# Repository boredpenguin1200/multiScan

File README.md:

# multiScan
Multispectral scanning using a 3d printer

This project is under heavy development, all hardware/software is experimental

software requires openCV with python bindings, tested/developed on linux but should be windows compatible

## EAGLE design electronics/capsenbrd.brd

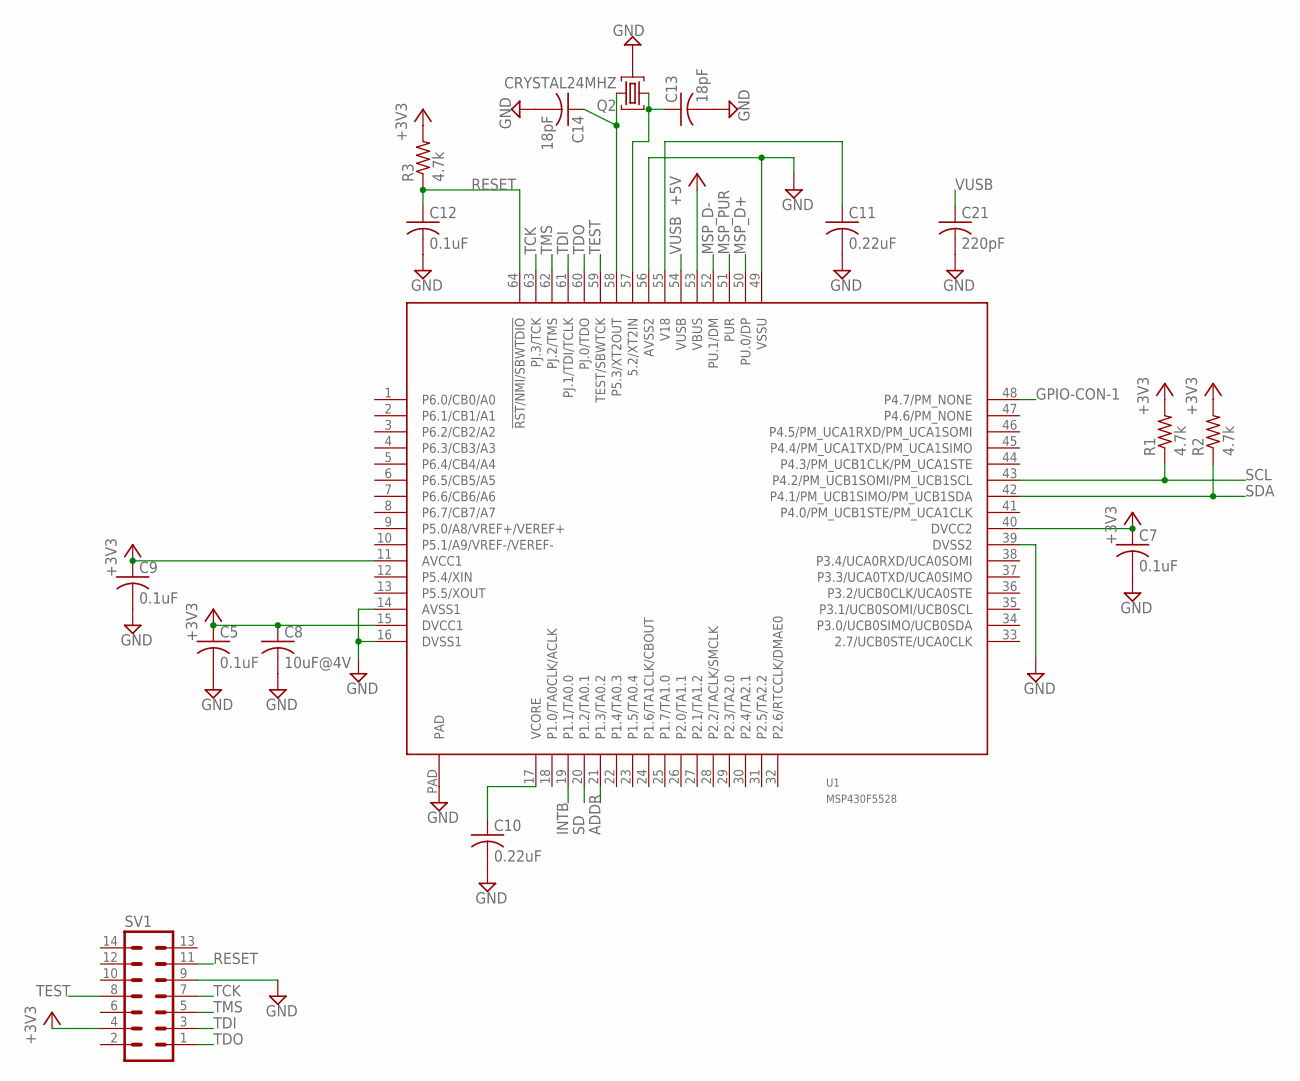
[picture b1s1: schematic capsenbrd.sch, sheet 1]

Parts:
C5, C7, C9, C12: 0.1uF; C0603
C8: 10uF@4V; C0603
C10, C11: 0.22uF; C0603
C13, C14: 18pF; C0603
C21: 220pF; C0603
Q2: CRYSTAL24MHZ; ABM8
R1, R2, R3: 4.7k; R0603
SV1: MA07-2SMT; MA07-2-SMT
U1: MSP430F5528; -RGC-N64

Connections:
+3V3: C5.1, C7.1, C8.1, C9.1, R1.2, R2.2, R3.2, SV1.4, U1.11 (AVCC1), U1.15 (DVCC1), U1.40 (DVCC2); also elsewhere on the board
+5V: U1.53 (VBUS); also elsewhere on the board
ADDR: U1.21 (P1.3/TA0.2); also elsewhere on the board
GND: C5.2, C7.2, C8.2, C9.2, C10.2, C11.2, C12.2, C13.2, C14.2, C21.2, Q2.2, Q2.4 (2), SV1.9, U1.14 (AVSS1), U1.16 (DVSS1), U1.39 (DVSS2), U1.49 (VSSU), U1.56 (AVSS2), U1.PAD; also elsewhere on the board
GPIO-CON-1: U1.48 (P4.7/PM_NONE); also elsewhere on the board
INTB: U1.19 (P1.1/TA0.0); also elsewhere on the board
MSP_D+: U1.50 (PU.0/DP); also elsewhere on the board
MSP_D-: U1.52 (PU.1/DM); also elsewhere on the board
MSP_PUR: U1.51 (PUR); also elsewhere on the board
unnamed: C11.1, U1.55 (V18)
unnamed: C10.1, U1.17 (VCORE)
unnamed: C13.1, Q2.1, U1.57 (5.2/XT2IN)
unnamed: C14.1, Q2.3, U1.58 (P5.3/XT2OUT)
RESET: C12.1, R3.1, SV1.11, U1.64 (!RST/NMI/SBWTDIO)
SCL: R1.1, U1.43 (P4.2/PM_UCB1SOMI/PM_UCB1SCL); also elsewhere on the board
SD: U1.20 (P1.2/TA0.1); also elsewhere on the board
SDA: R2.1, U1.42 (P4.1/PM_UCB1SIMO/PM_UCB1SDA); also elsewhere on the board
TCK: SV1.7, U1.63 (PJ.3/TCK)
TDI: SV1.3, U1.61 (PJ.1/TDI/TCLK)
TDO: SV1.1, U1.60 (PJ.0/TDO)
TEST: SV1.8, U1.59 (TEST/SBWTCK)
TMS: SV1.5, U1.62 (PJ.2/TMS)
VUSB: C21.1, U1.54 (VUSB)

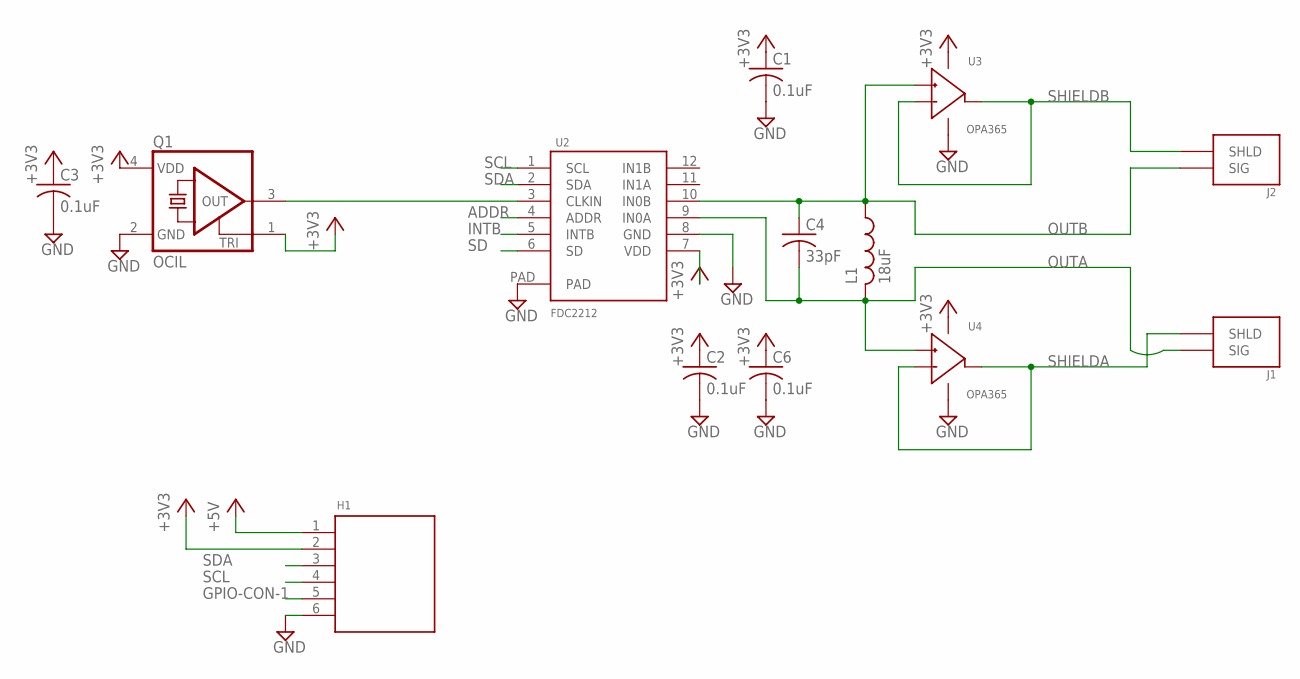
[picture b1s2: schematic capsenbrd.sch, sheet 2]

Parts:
C1, C2, C3, C6: 0.1uF; C0603
C4: 33pF; C0603
H1: CON-6-1; 10114828-10106LF
J1, J2: SMA-SMT-; 0732511352
L1: 18uF; L1210
Q1: OCIL; 625L3C040M00000
U2: FDC2212; -WSON
U3, U4: OPA365; -DBV

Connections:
+3V3: C1.1, C2.1, C3.1, C6.1, H1.2, Q1.1 (TRI), Q1.4 (VDD), U2.7 (VDD), U3.5 (V+), U4.5 (V+); also elsewhere on the board
+5V: H1.1; also elsewhere on the board
ADDR: U2.4 (ADDR); also elsewhere on the board
GND: C1.2, C2.2, C3.2, C6.2, H1.6, Q1.2 (GND), U2.8 (GND), U2.PAD, U3.2 (V-), U4.2 (V-); also elsewhere on the board
GPIO-CON-1: H1.5; also elsewhere on the board
INTB: U2.5 (INTB); also elsewhere on the board
unnamed: Q1.3 (OUT), U2.3 (CLKIN)
OUTA: C4.2, J1.SIG, L1.P$2 (2), U2.9 (IN0A), U4.3 (IN+)
OUTB: C4.1, J2.SIG, L1.P$1 (1), U2.10 (IN0B), U3.3 (IN+)
SCL: H1.4, U2.1 (SCL); also elsewhere on the board
SD: U2.6 (SD); also elsewhere on the board
SDA: H1.3, U2.2 (SDA); also elsewhere on the board
SHIELDA: J1.SHLD1 (SHLD), J1.SHLD2 (SHLD), J1.SHLD3 (SHLD), J1.SHLD4 (SHLD), U4.1 (VOUT), U4.4 (IN-)
SHIELDB: J2.SHLD1 (SHLD), J2.SHLD2 (SHLD), J2.SHLD3 (SHLD), J2.SHLD4 (SHLD), U3.1 (VOUT), U3.4 (IN-)

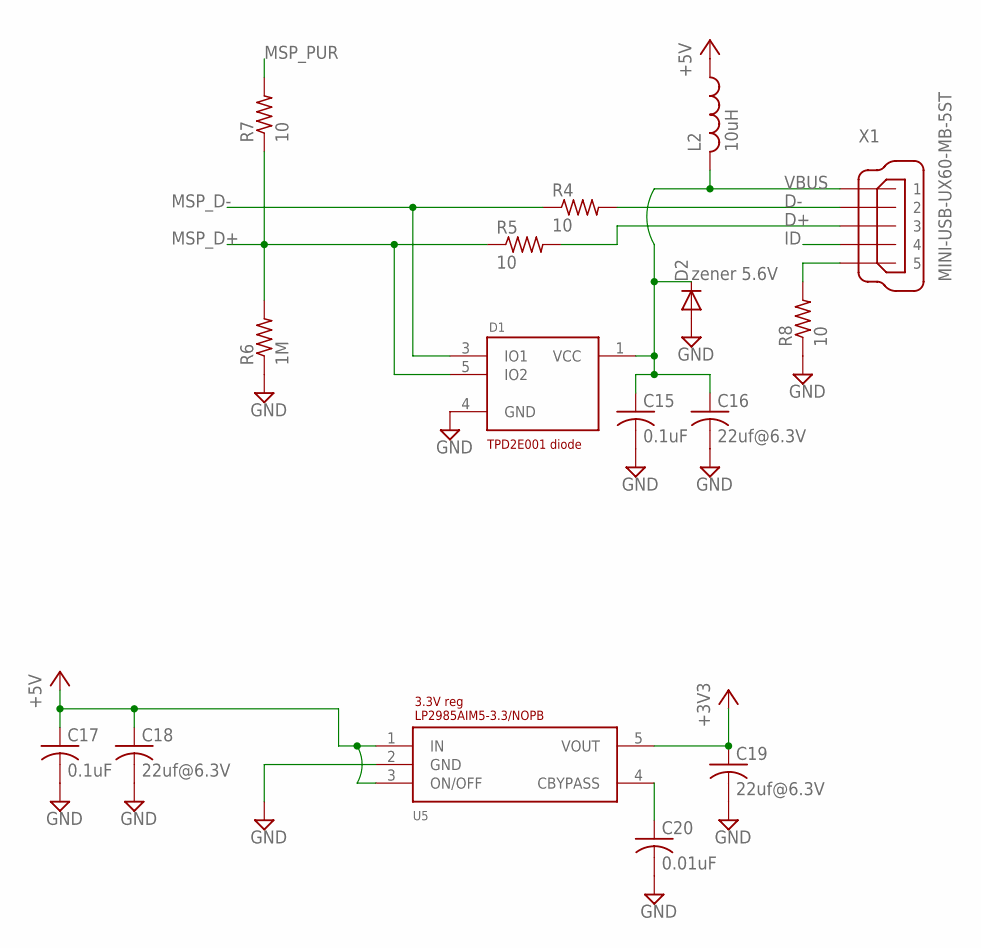
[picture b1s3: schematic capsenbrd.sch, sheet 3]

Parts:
C15, C17: 0.1uF; C0603
C16, C18, C19: 22uf@6.3V; C0603
C20: 0.01uF; C0603
D1: USB-DIODE; -DRL
D2: zener 5.6V; SOD123
L2: 10uH; VLS201610ET
R4, R5, R7, R8: 10; R0603
R6: 1M; R0603
U5: 3.3V; -DBV
X1: MINI-USB-UX60-MB-5ST; UX60-MB-5ST

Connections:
+3V3: C19.1, U5.5 (VOUT); also elsewhere on the board
+5V: C17.1, C18.1, L2.P$1 (1), U5.1 (IN), U5.3 (ON/OFF); also elsewhere on the board
D+: R5.2, X1.3
D-: R4.2, X1.2
GND: C15.2, C16.2, C17.2, C18.2, C19.2, C20.2, D1.4 (GND), D2.A, R6.1, R8.1, U5.2 (GND); also elsewhere on the board
ID: X1.4
MSP_D+: D1.5 (IO2), R5.1, R6.2, R7.1; also elsewhere on the board
MSP_D-: D1.3 (IO1), R4.1; also elsewhere on the board
MSP_PUR: R7.2; also elsewhere on the board
unnamed: R8.2, X1.5
unnamed: C20.1, U5.4 (CBYPASS)
VBUS: C15.1, C16.1, D1.1 (VCC), D2.C, L2.P$2 (2), X1.1

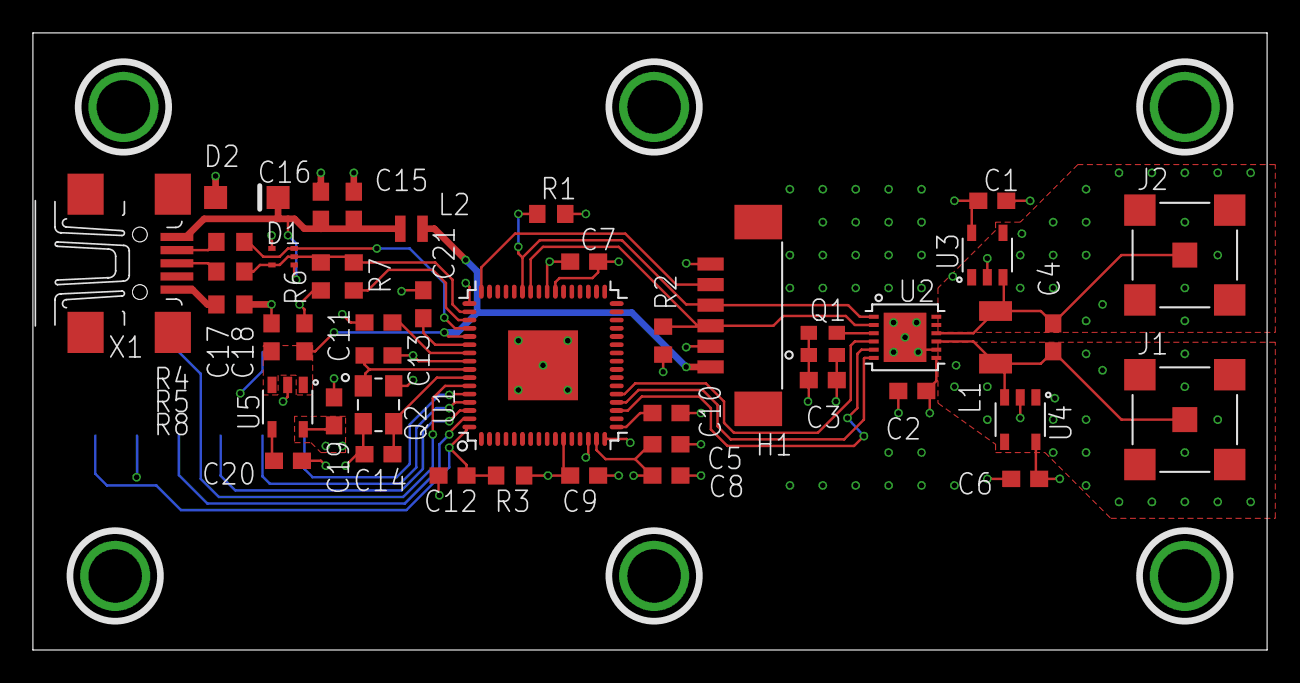
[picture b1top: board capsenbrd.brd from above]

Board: 4 copper layers, 75.0 x 37.5 mm, 45 parts (1 on the bottom side), 33 nets.

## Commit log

2016-12-10 inital commit after first scans
2016-12-10 inital mechanical import
2017-11-11 minor cleanup
    minor cleanup
